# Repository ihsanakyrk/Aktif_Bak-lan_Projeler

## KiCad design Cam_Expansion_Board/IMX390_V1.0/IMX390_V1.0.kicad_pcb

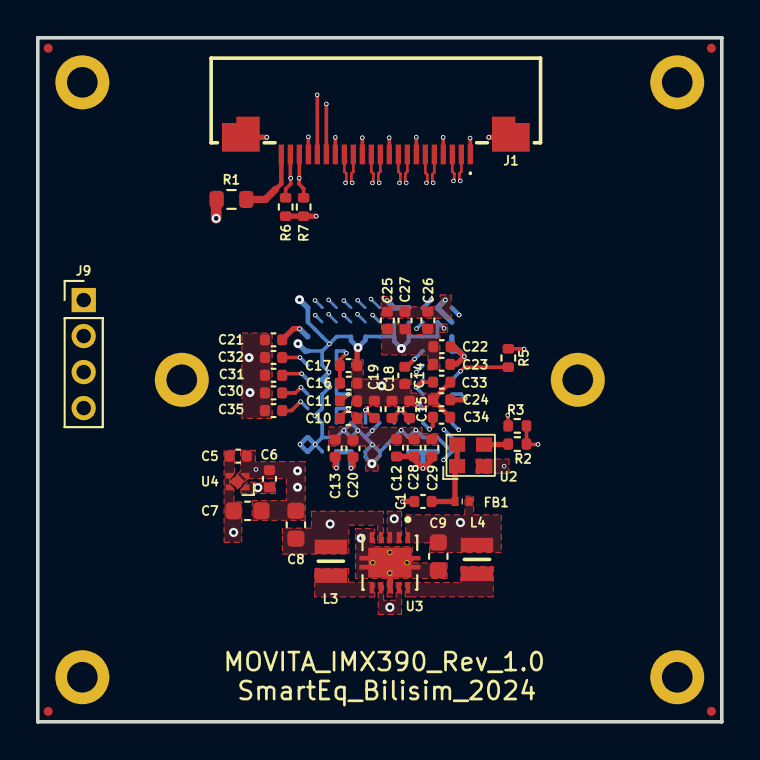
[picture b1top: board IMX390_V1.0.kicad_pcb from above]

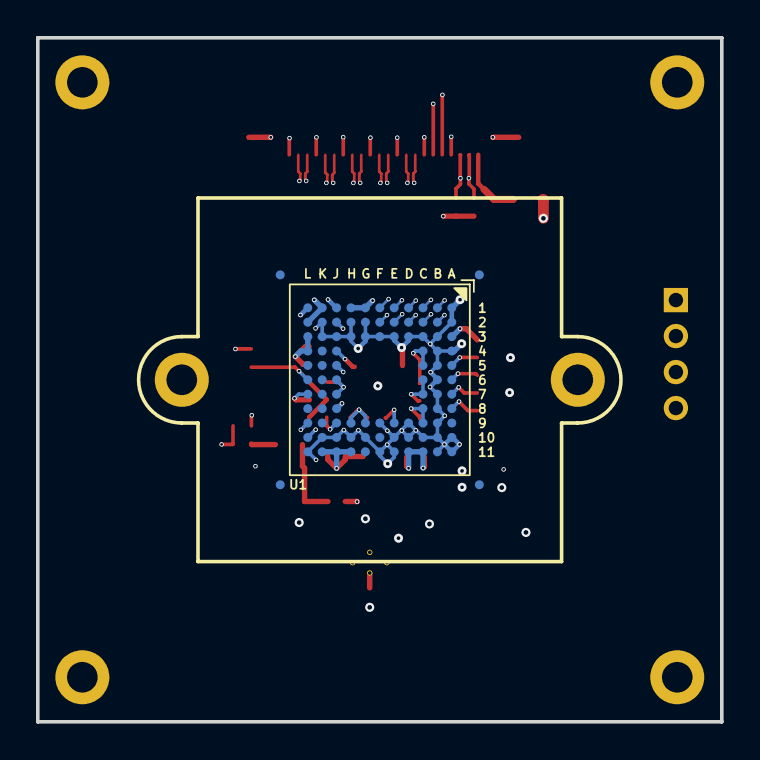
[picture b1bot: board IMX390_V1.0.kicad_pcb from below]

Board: 6 copper layers, 38.0 x 38.0 mm, 61 parts (5 on the bottom side), 33 nets.

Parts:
C1: 0.1uF 16V; C_0402_1005Metric
C5, C6, C10, C12, C18, C25, C28, C30, C31, C32, C34: 1.0µF 6.3V; C_0402_1005Metric
C7, C8, C9: 10uF 10V; C_0603_1608Metric
C11, C13, C15, C17, C19, C21, C23, C26, C29, C35: 0.1µF 16V; C_0402_1005Metric
C14, C16, C20, C22: 4.7µF 16V; C_0402_1005Metric
C24, C27: 0.01uF 6.3V; C_0402_1005Metric
C33: 0.22uF 10V; C_0402_1005Metric
FB1: BLM15AG221SN1D; NFZ15SG152SN10B
FID1, FID2, FID3, FID4, FID5, FID6, FID7, FID8: Fiducial; Fiducial_0.5mm_Mask1mm
J1: FFC SOCKET DR_BOTTOM 0.5MM -22P; F32R1A7H111022
J3, J4, J5, J6, J7, J8: DNP; Screw
J9: DNP; PinHeader_1x04_P2.00mm_Vertical
L3, L4: 2.2µH; LQM2MPN1R0NG0L
R1: 0R; R_0603_1608Metric
R2: 22R; R_0402_1005Metric
R3, R6, R7: DNP; R_0402_1005Metric
R5: 0R; R_0402_1005Metric
U1: IMX390CQV-W; IMX390CQV_W
U2: 1NM27000C33YC
U3: TPS62423QDRCRQ1; SON50P300X300X100-11N
U4: LP5907SNX-2.9/NOPB; X2-SON-4-EP

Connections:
1V2: C8.1, C12.1, C13.1, C20.1, C21.1, C25.1, C26.1, C27.2, C28.1, C29.1, L3.2, U1.A3 (VDDLSC), U1.C11 (VDDLCN), U1.D11 (VDDLSC), U1.G1 (VDDLIF), U1.H1 (VDDLIF), U1.H11 (VDDLCN), U1.J11 (VDDLPLAD), U1.K1 (VDDLSC), U1.K11 (VDDLPAD), U1.L2 (VDDLSC), U3.4 (FB1)
1V8: C9.1, C22.2, C23.2, C24.2, FB1.1, L4.2, R6.2, R7.2, U1.L3 (VDDMIO), U1.L4 (VDDMIO), U1.L7 (XCE), U3.1 (ADJ2)
2V9: C6.1, C10.1, C11.1, C14.1, C15.1, C16.1, C17.1, C18.1, C19.1, U1.C4 (VDDHPX), U1.C5 (VDDHCP), U1.C6 (VDDHCP), U1.C7 (VDDHAN), U1.C8 (VDDHAN), U1.C9 (VDDHPX), U1.E9 (VDDHCM), U1.G9 (VDDHCM), U1.H9 (VDDHPX), U1.J4 (VDDHPX), U4.1 (VOUT)
3V3: C5.1, C7.1, R1.1, U3.2 (MODE/DATA), U3.3 (VIN), U3.7 (EN1), U3.9 (EN2), U4.3 (EN), U4.4 (VIN)
/IMX390/CSI0_CLK_N: J1.8, U1.D2 (DMCKM)
/IMX390/CSI0_CLK_P: J1.9, U1.D1 (DMCKP)
/IMX390/CSI0_D0_N: J1.2, U1.E2 (DMOMA)
/IMX390/CSI0_D0_P: J1.3, U1.E1 (DMOPA)
/IMX390/CSI0_D1_N: J1.5, U1.C2 (DMOMB)
/IMX390/CSI0_D1_P: J1.6, U1.C1 (DMOPB)
/IMX390/CSI0_D2_N: J1.11, U1.F2 (DMOMC)
/IMX390/CSI0_D2_P: J1.12, U1.F1 (DMOPC)
/IMX390/CSI0_D3_N: J1.14, U1.B2 (DMOMD)
/IMX390/CSI0_D3_P: J1.15, U1.B1 (DMOPD)
/IMX390/EXT_XVCLK: J1.17, R3.2
/IMX390/FSIN: R5.1, U1.L6 (FSYNC)
/IMX390/SCL: J1.20, R7.1, U1.L10 (SCK)
/IMX390/SDA: J1.21, R6.1, U1.L9 (SDI)
/IMX390/SYS_CLEAR: J9.1, U1.J2 (XCLR)
/IMX390/XCLK: R2.2, R3.1, U1.J1 (INCK)
GND: C1.2, C5.2, C6.2, C7.2, C8.2, C9.2, C10.2, C11.2, C12.2, C13.2, C14.2, C15.2, C16.2, C17.2, C18.2, C19.2, C20.2, C21.2, C22.1, C23.1, C24.1, C25.2, C26.2, C27.1, C28.2, C29.2, C30.2, C31.2, C32.2, C33.2, C34.2, C35.2, J1.1, J1.4, J1.7, J1.10, J1.13, J1.16, J1.19, J1.23, J1.24, J3.1, J4.1, J5.1, J6.1, J7.1, J8.1, U1.A1 (VSSLSC), U1.A2 (VSSLSC), U1.A4 (VSSHCP), U1.A10 (VSSHCM), U1.A11 (VSSLSC), U1.B3 (VSSLIF), U1.B4 (VSSHPX), U1.B5 (VSSHCP), U1.B6 (VSSHCP), U1.B7 (VSSHAN), U1.B8 (VSSHAN), U1.B9 (VSSHPX), U1.B10 (VSSHCM), U1.B11 (VSSLSC), U1.C3 (VSSLIF), U1.C10 (VSSLCN), U1.D3 (VSSLIF), U1.D9 (VSSHCM), U1.D10 (VSSLSC), U1.E3 (VSSLIF), U1.E10 (SLASEL1), U1.E11 (SLASEL2), U1.F3 (VSSLIF), U1.F9 (VSSHCM), U1.F11 (SLASEL0), U1.G2 (VSSLIF), U1.G3 (VSSLIF), U1.G10 (CMODE), U1.H2 (VSSLSC), U1.H3 (VSSLSC), U1.H10 (VSSLCN), U1.J3 (VSSLSC), U1.J5 (VSSHPX), U1.J8 (VSSHPX), U1.J10 (VSSLPLAD), U1.K2 (VSSLSC), U1.K3 (VSSLSC), U1.K10 (VSSLPLAD), U1.L1 (VSSLSC), U1.L11 (VSSLSC), U2.2 (GND), U3.5 (DEF_1), U3.8 (GND), U3.11 (PAD), U4.2 (GND), U4.5 (EP)
unnamed: J1.18, R5.2
unnamed: J1.22, R1.2
unnamed: C32.1, U1.A5 (VCAPI1)
unnamed: C31.1, U1.A6 (VCAPI2)
unnamed: C30.1, U1.A7 (VCAPI3)
unnamed: C33.1, U1.J6 (VCAPI4), U1.J7 (VCAPI5)
unnamed: C34.1, U1.J9 (VCAPIO1)
unnamed: C35.1, U1.A8 (VCAPIO2)
unnamed: C1.1, FB1.2, U2.1 (OE), U2.4 (VDD)
unnamed: R2.1, U2.3 (OUT)
unnamed: L3.1, U3.6 (SW1)
unnamed: L4.1, U3.10 (SW2)

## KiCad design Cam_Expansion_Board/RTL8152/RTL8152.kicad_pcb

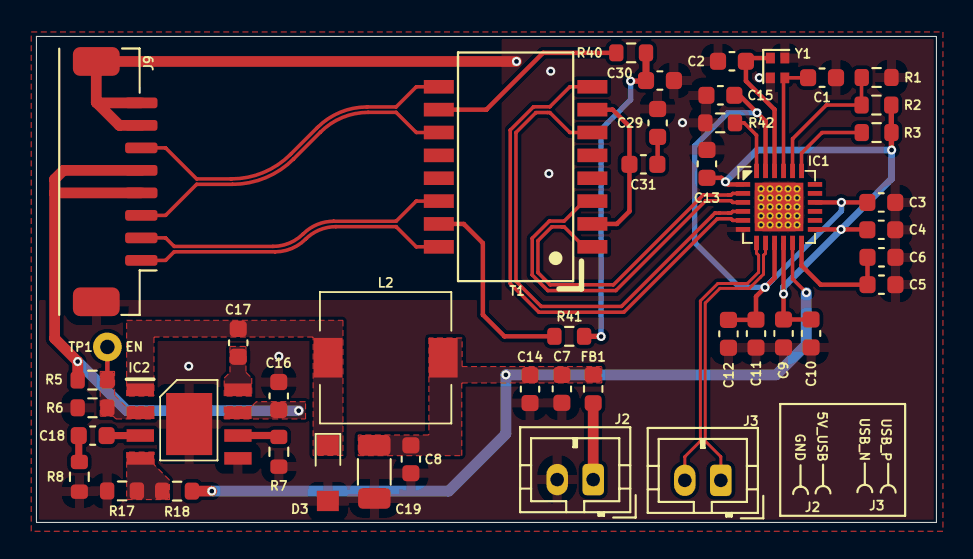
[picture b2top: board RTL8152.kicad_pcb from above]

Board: 2 copper layers, 50.0 x 27.0 mm, 45 parts (0 on the bottom side), 34 nets.

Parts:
C1, C2: 22pF; C_0603_1608Metric
C3, C4, C5, C7, C9, C11, C13, C15, C17: 100nF; C_0603_1608Metric
C6: 1uF; C_0603_1608Metric
C8, C10, C12: 4.7uF; C_0603_1608Metric
C14, C29, C31: 10nF; C_0603_1608Metric
C16: 10uF; C_0603_1608Metric
C18: 150pF; C_0603_1608Metric
C19: 22uF/6.3V; C_1206_3216Metric
C30: 1nF; C_0603_1608Metric
D3: SS34C-MD; SS34FA
FB1: BLM18AG102SN1D; 0603_Ferrite Beads
IC1: RTL8152B-VB-CG; QFN50P400X400X90-25N
IC2: MP1584EN-LF-Z; MP1584N
J2, J3: B2B-PH-K-S(LF)(SN); JST_PH_B2B-PH-K_1x02_P2.00mm_Vertical
J9: DS1020-03-08MVT1-R; JST_GH_BM08B-GHS-TBT_1x08-1MP_P1.25mm_Vertical
L2: SRI0704-100M
R1, R2, R3: 10K; R_0603_1608Metric
R5, R7, R8: 100K; R_0603_1608Metric
R6: 24.9K; R_0603_1608Metric
R17: 40.2K; R_0603_1608Metric
R18: 210K; R_0603_1608Metric
R40, R41, R42: 75R; R_0603_1608Metric
T1: H1102NL
TP1: DNP; Test_Point
Y1: RH100-25.000-20-F-1010-T; Oscillator_SMD_Abracon_ASCO-4Pin_1.6x1.2mm

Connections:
5V_LAN: C7.2 (-), C8.2 (-), C14.2 (-), C19.1, FB1.1, IC1.11 (VDD5), L2.2, R18.2
5V_USB: FB1.2, J2.1
/N1: IC1.3 (MDIN0), T1.3 (TD-)
/N2: IC1.5 (MDIN1), T1.8 (RD-)
/P1: IC1.2 (MDIP0), T1.1 (TD+)
/P2: IC1.4 (MDIP1), T1.6 (RD+)
/U2DN: IC1.7 (U2DM), J3.2
/U2DP: IC1.8 (U2DP), J3.1
/XIN_1: C2.1 (+), IC1.22 (CKXTAL2), Y1.1 (CRYSTAL_1)
/XOUT_1: C1.2 (-), IC1.21 (CKXTAL1), Y1.3 (CRSYTAL_2)
GND: C1.1 (+), C2.2 (-), C3.1 (+), C4.1 (+), C5.1 (+), C6.1 (+), C7.1 (+), C8.1 (+), C9.1 (+), C10.1 (+), C11.1 (+), C12.1 (+), C13.1 (+), C14.1 (+), C15.1 (+), C16.1, C19.2, C29.2, C30.2, D3.2, IC1.6 (U2GND), IC1.25 (EP), IC2.5 (GND), IC2.9 (EP), J2.2, J9.7, J9.8, J9.MP, R1.2, R6.2, R7.2, R8.2, R17.2, R42.2, Y1.2 (GND_1), Y1.4 (GND_2)
unnamed: C18.1, R8.1
unnamed: C29.1, C31.2
unnamed: C30.1, R40.1, R41.2
unnamed: IC1.19 (LANWAKEB), R3.1
unnamed: IC1.24 (RSET), R42.1
unnamed: IC1.20 (SPISDO), R1.1, R2.1
unnamed: C17.2, IC2.8 (BST)
unnamed: C18.2, IC2.3 (COMP)
unnamed: IC2.2 (EN), R5.2, R6.1, TP1.1
unnamed: IC2.4 (FB), R17.1, R18.1
unnamed: IC2.6 (FREQ), R7.1
unnamed: C17.1, D3.1, IC2.1 (SW), L2.1
unnamed: C31.1, T1.2 (CT1), T1.7 (CT2)
unnamed: R40.2, T1.10 (CT3)
unnamed: R41.1, T1.15 (CT4)
TRD0_N: J9.2, T1.14 (TX-)
TRD0_P: J9.1, T1.16 (TX+)
TRD1_N: J9.6, T1.9 (RX-)
TRD1_P: J9.3, T1.11 (RX+)
VDD3V3: C4.2 (-), C9.2 (-), C10.2 (-), C13.2 (-), IC1.1 (AVDD33_1), IC1.10 (AVDD33_2), IC1.13 (DVDD33), R2.2, R3.2
VDD10: C3.2 (-), C11.2 (-), C12.2 (-), C15.2 (-), IC1.9 (U2VDD10), IC1.16 (DVDD10), IC1.23 (AVDD10)
VDD10_UPS: C5.2 (-), C6.2 (-), IC1.12 (DVDD10_UPS)
VRAW: C16.2, IC2.7 (VIN), J9.4, J9.5, R5.1

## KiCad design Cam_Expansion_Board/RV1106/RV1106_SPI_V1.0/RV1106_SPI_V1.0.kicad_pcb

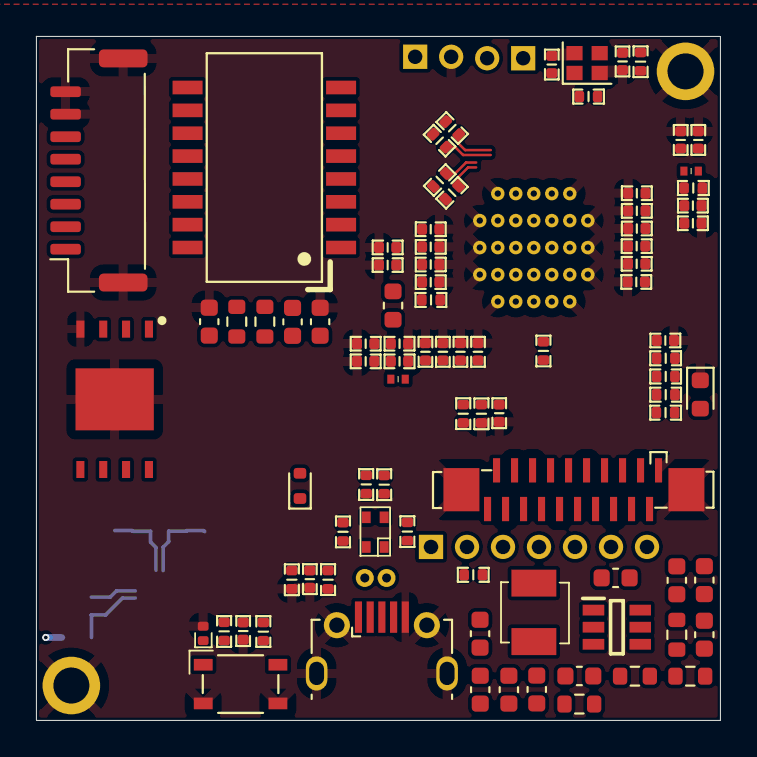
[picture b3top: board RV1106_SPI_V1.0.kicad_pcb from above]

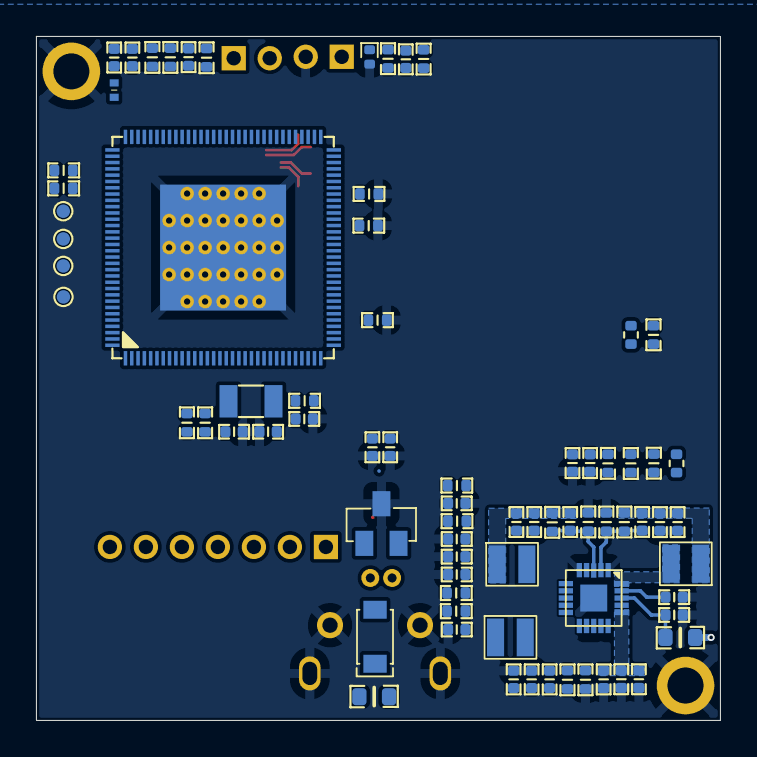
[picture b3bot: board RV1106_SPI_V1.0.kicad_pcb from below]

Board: 4 copper layers, 38.0 x 38.0 mm, 170 parts (76 on the bottom side), 110 nets.

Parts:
C1, C2, C6, C7: 18pF 50V C0G; C_0402_1005Metric
C3, C4, C5, C9, C10, C11, C16, C17, C18, C21, C25, C27, C29, C34, C36, C50, C51, C52, C54, C55, C72: 100nF X5R 16V; C_0402_1005Metric
C8, C14, C15, C20, C24, C26, C73: 1uF X5R 6.3V; C_0402_1005Metric
C12, C13, C19, C22, C23, C28, C62: 10uF X5R 6.3V; C_0402_1005Metric
C35: DNP; C_0402_1005Metric
C37, C42, C45: 220pF; C_0402_1005Metric
C38, C39, C43: 4.7uF; C_0402_1005Metric
C40, C41, C44, C46, C47, C48, C49: 10uF 10V; C_0402_1005Metric
C53, C71: 4.7uF X5R 6.3V; C_0402_1005Metric
C63: 100nF X5R 6.3V; C_0402_1005Metric
C74, C75: 0.01uF; C_0603_1608Metric
C76: 1000pF; C_0603_1608Metric
C77, C78, C79, C81: 1nF C0G 50V; C_0402_1005Metric
C80, C82: 10uF 25V X5R; C_0603_1608Metric
C84: 100nF; C_0603_1608Metric
C85: 22pF; C_0603_1608Metric
C86, C87: 22uF 16V X5R; C_0603_1608Metric
C88, C89, C90: 100nF 16V X5R; C_0603_1608Metric
D1: RB521S-30; D_SOD-523
D2: LED_White; LED_0603_1608Metric
D32: MBR230LSFT1G; SS14
D34, D35: ESD5451N; ESD5341N
ESD1: ESD5302F; SOT-23-Diode
FB1: DNP; SMD-4P,2.0x1.2mm
IC3: SY8113B
J1, J3: DNP; Min_Screw
J2: DNP; PinHeader_1x07_P2.00mm_Vertical
J4, J5: DNP; PinHeader_1x02_P2.00mm_Vertical
J13: JST_1x8-1MP_P1.25mm_Vertical; JST_1x8_1MP_P1.25mm_Vertical
J20: MICRO XNJ ZB; Micro-B SMD
J28: AFC11-S20ICA-00
L1, L2, L7: BLM15PD121SN1; Feritte_Beads_0402
L4, L5, L6: FTC252012S1R5MBCA
L8: CBG160808U000T; 0603_Ferrite Beads
L9: HA42-4R7MT
R1: 1M %5; R_0402_1005Metric
R2, R4, R6, R7, R21, R22: 22R %5; R_0402_1005Metric
R3, R28, R42: 100R %5; R_0402_1005Metric
R5, R26: 1R %5; R_0402_1005Metric
R10, R18, R25, R29, R30, R31, R32, R48, R49, R57, R58, R61, R63, R69: 0R; R_0402_1005Metric
R11: 100K %5; R_0603_1608Metric
R12, R27, R55, R56, R59: 10K %5; R_0402_1005Metric
R13: 200K; R_0402_1005Metric
R14: 40.2K %1; R_0402_1005Metric
R15: 9.1K %1; R_0402_1005Metric
R16: 47K %1; R_0402_1005Metric
R17, R20: 100K %1; R_0402_1005Metric
R19: 200K %1; R_0402_1005Metric
R23: 240R %1; R_0402_1005Metric
R24: 6.04K %1; R_0402_1005Metric
R33: 1K %5; R_0402_1005Metric
R43, R44: 4.7K %5; R_0402_1005Metric
R45: DNP; R_0603_1608Metric
R46, R47: 2.2R %5; R_0402_1005Metric
R50, R60, R62, R66, R67, R68: DNP; R_0402_1005Metric
R64: 10K; R_0402_1005Metric
R65: 15K; R_0402_1005Metric
R70, R71: 75R; R_0603_1608Metric
R75: 110K; R_0603_1608Metric
R76: 15K; R_0603_1608Metric
R77: 120K; R_0603_1608Metric
R78: 30K; R_0603_1608Metric
S5: SKRPANE010
T1: H1102NL
TP1, TP2: DNP; Test_Point
TP6, TP7, TP8, TP9: DNP; TestPoint_Pad_D0.75
U1: RV1106G3
U3: EA3036C
U5: W25N02KVZEIR; SON127P800X600X80-9N-D
U7: 24MHz; Crystal_SMD_2016-4Pin_2.0x1.6mm
Y1: Crystal_32.768kHz; Crystal_SMD_3215-2Pin_3.2x1.5mm

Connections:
/DN: ESD1.2, FB1.4, J20.2 (DM), R48.2, TP1.1
/DP: ESD1.1, FB1.1, J20.3 (DP), R49.2, TP2.1
/EN1: C36.1, R13.2, U3.9 (EN1)
/EN2: C35.1, R12.2, U3.8 (EN2)
/EN3: C34.1, R11.2, U3.18 (EN3)
/ETH_R_N: R32.1, U1.97 (FEPHY_RXN)
/ETH_R_P: R31.1, U1.98 (FEPHY_RXP)
/ETH_T_N: R30.1, U1.99 (FEPHY_TXN)
/ETH_T_P: R29.1, U1.100 (FEPHY_TXP)
/FSPI_CLK: R21.1, U5.6 (CLK)
/FSPI_CS0N: U1.47 (FSPI_CS0_EMMC_CMD_GPIO4_B0_u), U5.1 (~CS)
/FSPI_D0: R67.2, U1.41 (FSPI_D0_EMMC_D0_GPIO4_A4_u), U5.5 (DI(D0))
/FSPI_D1: R68.2, U1.42 (FSPI_D1_EMMC_D1_GPIO4_A3_u), U5.2 (DO(D1))
/FSPI_D2: R55.2, U1.44 (FSPI_D2_EMMC_D2_GPIO4_A2_u), U5.3 (~WP(D2))
/FSPI_D3: R56.2, U1.39 (FSPI_D3_EMMC_D3_GPIO4_A6_u), U5.7 (~HOLD(D3))
/GPIO3_C6_d: R7.2, R50.1, U1.4 (VI_BT656_D2_M0_VI_BT1120_D10_PWM7_IR_M2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)
/GPIO4_C1_z: C79.1, R59.2, R60.1, U1.22 (PWM1_M1_SARADC_IN1_GPIO4_C1_z)
/MIPI_CSI_AVDD_1V8: C11.1, R5.2, U1.1 (MIPI_AVDD1V8_VCCIO7_VCC1V8)
/MIPI_I2C_SCL: J28.13, R43.1, U1.5 (VI_BT656_D3_M0_VI_BT1120_D11_UART5_TX_M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)
/MIPI_I2C_SDA: J28.14, R44.1, U1.7 (VI_BT656_D4_M0_VI_BT1120_D12_UART5_RX_M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)
/MIPI/LVDS_CLK_N: J28.8, U1.125 (VI_BT656_D0_M0_VI_BT1120_D8_LVDS_RX_CLK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)
/MIPI/LVDS_CLK_P: J28.7, U1.126 (VI_BT656_D1_M0_VI_BT1120_D9_LVDS_RX_CLK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)
/MIPI/LVDS_D0_N: J28.5, U1.127 (VI_BT656_CLK_M0_VI_BT1120_CLK_LVDS_RX_D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)
/MIPI/LVDS_D0_P: J28.4, U1.128 (LVDS_RX_D0P_MIPI_CSI_RX_D0P_VI_CIF_HREF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)
/MIPI/LVDS_D1_N: J28.11, U1.123 (VI_BT1120_D6_LVDS_RX_D1N_MIPI_CSI_RX_D1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)
/MIPI/LVDS_D1_P: J28.10, U1.124 (VI_BT1120_D7_LVDS_RX_D1P_MIPI_CSI_RX_D1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)
/MIPI/LVDS_MCLK0: J28.2, R6.1
/MIPI/LVDS_RST: J28.16, U1.3 (VI_CIF_VSYNC_M0_GPIO3_C5_d)
/NPOR: C78.1, R33.2, R42.1, U1.66 (nPOR)
/RECOVERY: C77.1, R27.2, R28.1, U1.23 (SARADC_IN0_GPIO4_C0_z)
/RX_P0+: R31.2, T1.6 (RD+)
/RX_P0-: R32.2, T1.8 (RD-)
/SDMMC_CLK: J2.4, R22.1
/SDMMC_CMD: J2.3, U1.16 (JTAG_LPMCU_TMS_M1_I2C0_SDA_M2_PWM11_IR_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)
/SDMMC_D0: J2.5, U1.14 (PWM8_M0_UART2_RX_M0_SDMMC_D0_GPIO3_A3_u)
/SDMMC_D1: J2.6, U1.12 (PWM9_M0_UART2_TX_M0_SDMMC_D1_GPIO3_A2_u)
/SDMMC_D2: J2.1, U1.18 (JTAG_HPMCU_TCK_M1_JTAG_CPU_TCK_M0_UART5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)
/SDMMC_D3: J2.2, U1.17 (JTAG_HPMCU_TMS_M1_JTAG_CPU_TMS_M0_UART5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)
/SDMMC_DET: J2.7, U1.11 (SDMMC_DET_GPIO3_A1_u)
/TX_P0+: R29.2, T1.1 (TD+)
/TX_P0-: R30.2, T1.3 (TD-)
/UART1_CTS: TP7.1, U1.109 (I2C4_SDA_M0_UART1_CTS_M1_VO_LCDC_D8_I2S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)
/UART1_RTS: TP6.1, U1.110 (I2C4_SCL_M0_UART1_RTS_M1_VO_LCDC_D9_I2S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)
/UART1_RX: TP8.1, U1.114 (UART1_RX_M1_VO_LCDC_D13_I2S0_SDI0_SDIO_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)
/UART1_TX: TP9.1, U1.113 (UART1_TX_M1_VO_LCDC_D12_I2S0_SDO0_SDIO_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)
/UART2_RX: J4.1, U1.80 (JTAG_HPMCU_TMS_M0_JTAG_LPMCU_TMS_M0_JTA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)
/UART2_TX: J4.2, U1.79 (JTAG_HPMCU_TCK_M0_JTAG_LPMCU_TCK_M0_JTA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)
/USB_DET_IN: C81.1, R64.2, R65.1, U1.25 (USB_VBUSDET)
/USB_N: R46.1, U1.26 (USB_DM)
/USB_P: R47.1, U1.27 (USB_DP)
/USB_VIN: D32.A, J20.1 (VBUS), R64.1
Earth: C80.1, C82.1, C86.1, C87.1, C88.1, C89.1, C90.1, IC3.2 (GND), R76.2, R78.2
GND: C1.2, C2.1, C3.2, C4.2, C5.2, C6.2, C7.2, C8.2, C9.2, C10.2, C11.2, C12.2, C13.2, C14.2, C15.2, C16.2, C17.2, C18.2, C19.2, C20.2, C21.2, C22.2, C23.2, C24.2, C25.2, C26.2, C27.2, C28.2, C29.2, C34.2, C35.2, C36.2, C38.1, C39.1, C40.1, C41.1, C43.1, C44.1, C46.2, C47.2, C48.2, C49.2, C50.2, C51.2, C52.2, C53.2, C54.2, C55.2, C62.2, C63.2, C71.2, C72.2, C73.2, C75.2, C76.2, C77.2, C78.2, C79.2, C81.2, D2.1, D34.2, D35.2, ESD1.3, J1.1, J3.1, J5.2, J13.7, J13.8, J13.9, J13.10, J20.5 (GND), J20.6 (Shield), J28.1, J28.3, J28.6, J28.9, J28.12, J28.15, J28.17, J28.18, J28.21, J28.22, R15.2, R17.2, R20.2, R23.2, R24.2, R25.1, R58.1, R60.2, R65.2, S5.3, S5.4, U1.129 (ePAD), U3.1 (GND3), U3.4 (GND2), U3.5 (GND2), U3.12 (GND1), U3.13 (GND1), U3.15 (AGND), U3.17 (AGND), U3.21 (AGND), U5.4 (VSS), U5.9 (EPAD), U7.2 (GND), U7.4 (GND)
unnamed: C74.2, C75.1
unnamed: C76.1, R70.1, R71.1
unnamed: D1.1 (K), R3.1
unnamed: D2.2, R50.2
unnamed: D32.C, R45.2
unnamed: D34.1, R28.2, S5.1, S5.2
unnamed: FB1.2, R47.2, R49.1
unnamed: FB1.3, R46.2, R48.1
unnamed: C84.1, IC3.1 (BS)
unnamed: IC3.4 (EN), R77.2, R78.1
unnamed: C85.1, IC3.3 (FB), R75.2, R76.1
unnamed: C84.2, IC3.6 (LX), L9.1
unnamed: D35.1, J5.1, R42.2
unnamed: J28.19, J28.20, R10.1
unnamed: C74.1, T1.2 (CT1), T1.7 (CT2)
unnamed: R70.2, T1.10 (CT3)
unnamed: R71.2, T1.15 (CT4)
unnamed: C6.1, U1.21 (OSC_RTC_XIN), Y1.1
unnamed: C7.1, U1.20 (OSC_RTC_XOUT), Y1.2
unnamed: C2.2, R1.1, U1.68 (OSC_SOC_XIN), U7.1 (X1)
unnamed: R1.2, R2.2, U1.69 (OSC_SOC_XOUT)
unnamed: L1.1, U1.96 (OTP_AVDD1V8_ETH_AVDD1V8_TSADC_AVDD1V8)
unnamed: C8.1, R3.2, U1.19 (RTC_AVDD3V3)
unnamed: R58.2, U1.57 (TVSS)
unnamed: R21.2, U1.48 (FSPI_CLK_EMMC_CLK_GPIO4_B1_d)
unnamed: R22.2, U1.15 (JTAG_LPMCU_TCK_M1_I2C0_SCL_M2_PWM10_M0_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)
unnamed: C50.1, R57.2, U1.43 (VCCIO3_VCC)
unnamed: R4.2, U1.85 (I2C3_SCL_M1_AUD_DSM_N_UART5_TX_M1_PWM11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)
unnamed: R6.2, U1.2 (MIPI_CLK0_OUT_VI_CIF_CLKO_M0_GPIO3_C4_d)
unnamed: R61.2, R62.2, U1.108 (VCCIO5_VCC)
unnamed: R63.2, R66.2, U1.88 (VCCIO6_VCC)
unnamed: R25.2, U1.37 (CODEC_AVSS)
unnamed: C53.1, U1.30 (CODEC_VCM)
unnamed: R23.1, U1.52 (DRAM_ZQ)
unnamed: L7.2, U1.101 (FEPHY_AVDD3V3)
unnamed: R24.1, U1.102 (FEPHY_REXT)
unnamed: C54.1, R26.2, U1.24 (SARADC_USB_AVDD1V8)
unnamed: C37.2, R14.1, R15.1, U3.14 (FB1)
unnamed: C42.2, R16.1, R17.1, U3.3 (FB2)
unnamed: C45.2, R19.1, R20.1, U3.2 (FB3)
unnamed: L5.2, U3.6 (LX2)
unnamed: L6.2, U3.20 (LX3)
unnamed: L4.2, U3.11 (LX)
unnamed: R69.1, U5.8 (VCC)
unnamed: C1.1, R2.1, U7.3 (X2)
RX0_N: J13.6, T1.9 (RX-)
RX0_P: J13.3, T1.11 (RX+)
TRD0_N: J13.2, T1.14 (TX-)
TRD0_P: J13.1, T1.16 (TX+)
VCC1V8_CODEC: C28.1, C29.1, L2.2, U1.31 (CODEC_AVDD1V8)
VCC5V0_SYS: C46.1, C47.1, C48.1, C49.1, C85.2, C86.2, C87.2, C88.2, C89.2, L9.2, R11.1, R12.1, R13.1, R45.1, R75.1, U3.7 (VIN2), U3.10 (VIN1), U3.16 (VCC), U3.19 (VIN3)
VCC_1V8: C3.1, C4.1, C26.1, C27.1, C71.1, C72.1, L1.2, L2.1, L8.1, R5.1, R26.1, R27.1, R43.2, R44.2, R59.1, R62.1, R66.1, U1.53 (DDR_PLL_AVDD1V8), U1.70 (OSC_AVDD1V8_PLL_AVDD1V8)
VCC_3V3: C9.1, C10.1, C37.1, C38.2, C39.2, C51.1, C52.1, C55.1, C62.1, C63.1, D1.2 (A), L4.1, L7.1, R10.2, R14.2, R33.1, R55.1, R56.1, R57.1, R61.1, R63.1, R67.1, R68.1, R69.2, U1.13 (VCCIO4_VCC), U1.28 (USB_AVDD3V3), U1.61 (PMU_VCC3V3), U1.81 (VCCIO1_VCC3V3)
VCC_DDR: C22.1, C23.1, C24.1, C25.1, C43.2, C44.2, C45.1, C73.1, L6.1, L8.2, R19.2, U1.49 (DDR_VDDQ_1), U1.50 (DDR_VDDQ_2), U1.56 (DDR_VDDQ_3)
VDD_0V9: C5.1, C12.1, C13.1, C14.1, C15.1, C16.1, C17.1, C18.1, C40.2, C41.2, C42.1, L5.1, R16.2, R18.1, U1.10 (DVDD_1), U1.51 (DVDD_2), U1.54 (DVDD_3), U1.55 (DVDD_4), U1.67 (OSC_DVDD0V9_PMU_DVDD0V9), U1.71 (PLL_DVDD0V9), U1.82 (DVDD_5), U1.103 (DVDD_6), U1.116 (DVDD_7)
VDD_ARM: C19.1, C20.1, C21.1, R18.2, U1.115 (CPU_DVDD)
VIN: C80.2, C82.2, C90.2, IC3.5 (IN), J13.4, J13.5, R77.1

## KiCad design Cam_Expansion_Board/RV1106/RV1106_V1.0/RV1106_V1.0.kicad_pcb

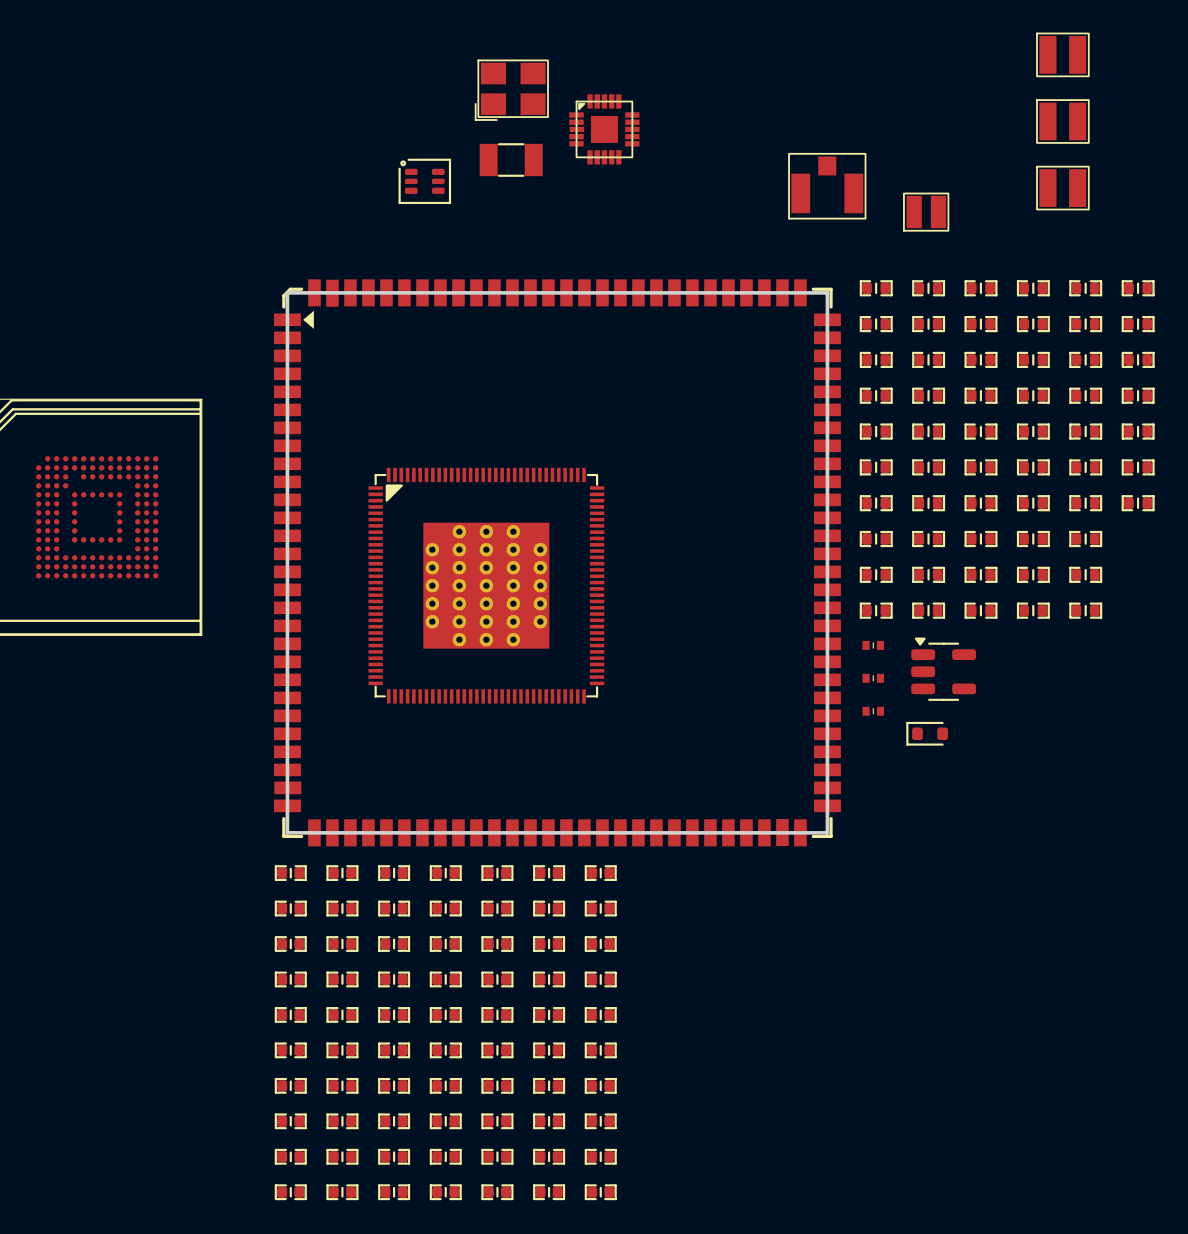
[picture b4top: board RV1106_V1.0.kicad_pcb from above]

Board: 2 copper layers, 144 parts (0 on the bottom side), 163 nets, no tracks yet.

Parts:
C1, C2: 18pF C0G; C_0402_1005Metric
C3, C4: 100nF X5R; C_0402_1005Metric
C5, C9, C10, C11, C16, C17, C18, C21, C25, C27, C29, C34, C36, C50, C51, C52, C54, C55, C63, C64, C65, C66, C68, C69: 100nF 16V X5R; C_0402_1005Metric
C6, C7: 18pF 50V C0G; C_0402_1005Metric
C8, C14, C15, C20, C24, C26, C62: 1uF 6.3V X5R; C_0402_1005Metric
C12, C13, C19, C22, C23, C28: 10uF 6.3V X5R; C_0402_1005Metric
C30, C46, C47, C48, C49: 10uF 10V; C_0402_1005Metric
C31, C33: 100nF; C_0402_1005Metric
C32, C40, C41, C44, C56, C59, C61: 10uF; C_0402_1005Metric
C35, C58: DNP; C_0402_1005Metric
C37, C42, C45: 220pF; C_0402_1005Metric
C38, C39, C43: 4.7uF; C_0402_1005Metric
C53, C67, C70: 4.7uF 6.3V X5R; C_0402_1005Metric
C57: 10pF; C_0402_1005Metric
C60: 10uF/10V; C_0402_1005Metric
D1: RB521S-30; D_SOD-523
J1: IPEX1-3-TXZ 214
L1, L2, L7: BLM15PD121SN1; Feritte_Beads_0402
L3: PIM201610-1R0MTS00; SMD,2x1.6x1mm_Power_Inductor
L4, L5, L6: FTC252012S1R5MBCA
R1: 1M %5; R_0402_1005Metric
R2, R4, R6, R7, R21, R22: 22R %5; R_0402_1005Metric
R3: 100R %5; R_0402_1005Metric
R5, R26: 1K %5; R_0402_1005Metric
R8: 100K; R_0402_1005Metric
R9: 100K %1; R_0402_1005Metric
R10: 127K %1; R_0402_1005Metric
R11: 100K %5; R_0402_1005Metric
R12, R55, R56: 10K %5; R_0402_1005Metric
R13: 200K; R_0402_1005Metric
R14: 40.2K %1; R_0402_1005Metric
R15: 9.1K %1; R_0402_1005Metric
R16: 47K %1; R_0402_1005Metric
R17, R20: 100K 1%; R_0402_1005Metric
R18, R25: 0R %5; R_0402_1005Metric
R19: 200K %1; R_0402_1005Metric
R23: 240R %1; R_0402_1005Metric
R24: 6.04K %1; R_0402_1005Metric
R27, R28: 4.7K; R_0402_1005Metric
R29: 10K; R_0402_1005Metric
R30, R31, R32, R33: 1K; R_0402_1005Metric
R34, R35, R36, R37, R38, R39, R40, R41, R42, R43, R44, R45, R46, R47, R48, R49, R50, R51, R52, R53, R54: 0R; R_0402_1005Metric
R57: 4.7K %5; R_0402_1005Metric
U1: RV1106G3
U2: MP1605GTF-Z; SOT-563
U3: EA3036C
U5: DNP; Core1106-SMT
U7: 24MHz; SMD3225-4P
U8: ME6217C33M5G; SOT-23-5
U9: EMMC_B153_2L; EMMC
Y1: Crystal_32.768kHz; Crystal_SMD_3215-2Pin_3.2x1.5mm

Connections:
3V3: C56.1, C59.1, C61.1, R27.2, R28.2, U8.5 (OUT)
/EMMC_CLK: R21.1, R43.2, U9.M6 (CLK)
/EMMC_CMD: R42.2, U1.47 (FSPI_CS0_EMMC_CMD_GPIO4_B0_u)
/EMMC_D0: R34.2, R55.1, U1.41 (FSPI_D0_EMMC_D0_GPIO4_A4_u), U9.A3 (DATA0)
/EMMC_D1: R35.2, U1.42 (FSPI_D1_EMMC_D1_GPIO4_A3_u), U9.A4 (DATA1)
/EMMC_D2: R36.2, U1.44 (FSPI_D2_EMMC_D2_GPIO4_A2_u), U9.A5 (DATA2)
/EMMC_D3: R37.2, U1.39 (FSPI_D3_EMMC_D3_GPIO4_A6_u), U9.B2 (DATA3)
/EMMC_D4: R38.2, U1.40 (SPI1_CS0_M0_I2C2_SDA_M1_UART1_TX_M2_EMM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), U9.B3 (DATA4)
/EMMC_D5: R39.2, U1.38 (SPI1_CLK_M0_I2C2_SCL_M1_UART1_RX_M2_EMM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), U9.B4 (DATA5)
/EMMC_D6: R40.2, U1.45 (SPI1_MOSI_M0_I2C0_SCL_M1_UART0_TX_M2_EM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), U9.B5 (DATA6)
/EMMC_D7: R41.2, R56.1, U1.46 (SPI1_MISO_M0_I2C0_SDA_M1_UART0_RX_M2_EM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), U9.B6 (DATA7), U9.M5 (CMD)
/EN1: C36.1, R13.2, U3.9 (EN1)
/EN2: C35.1, R12.2, U3.8 (EN2)
/EN3: C34.1, R11.2, U3.18 (EN3)
/ETH_R_N: U1.97 (FEPHY_RXN), U5.85
/ETH_R_P: U1.98 (FEPHY_RXP), U5.86
/ETH_T_N: U1.99 (FEPHY_TXN), U5.87
/ETH_T_P: U1.100 (FEPHY_TXP), U5.88
/FLASH_ALE/EMMC_RST: R57.1, U9.K5 (RST_n)
/GPIO0_A0_z: U1.58 (RTC_CLK_OUT_CLK_32K_IN_REF_CLK_OUT_UART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), U5.58
/GPIO0_A1_d: U1.59 (PWM2_M0_UART0_TX_M0_GPIO0_A1_d), U5.59
/GPIO0_A2_d: R32.1, U1.60 (PWM3_IR_M0_GPIO0_A2_d), U5.60
/GPIO0_A3_u: R31.1, U1.62 (PWR_CTRL_M1_GPIO0_A3_u), U5.61
/GPIO0_A4_d: R30.1, U1.63 (PWM1_M0_PWR_CTRL_M0_GPIO0_A4_d), U5.62
/GPIO0_A5_d: R51.2, U1.64 (I2C1_SCL_M0_PWM5_M0_UART1_RTS_M0_GPIO0_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)
/GPIO0_A6_d: R52.2, U1.65 (I2C1_SDA_M0_PWM6_M0_UART1_CTS_M0_GPIO0_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)
/GPIO1_A0_d: U1.72 (I2C2_SCL_M0_PWM7_IR_M0_UART3_TX_M0_GPIO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), U5.65
/GPIO1_A1_d: U1.73 (I2C2_SDA_M0_PWM4_M0_UART3_RX_M0_GPIO1_A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), U5.66
/GPIO1_A2_d: R33.1, U1.74 (VI_CIF_D0_M1_CPU_AVS_PWM0_M0_GPIO1_A2_d), U5.67
/GPIO1_A3_d: R54.2, U1.75 (I2C0_SCL_M0_UART1_TX_M0_GPIO1_A3_d)
/GPIO1_A4_d: R53.2, U1.76 (I2C0_SDA_M0_UART1_RX_M0_GPIO1_A4_d)
/GPIO1_B0_d: U1.77 (PWM3_IR_M1_UART4_RX_M0_GPIO1_B0_d), U5.70
/GPIO1_B1_d: U1.78 (SPI1_CS1_M0_VI_CIF_D1_M1_PWM7_IR_M1_UAR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), U5.71
/GPIO1_B2_d: U1.79 (JTAG_HPMCU_TCK_M0_JTAG_LPMCU_TCK_M0_JTA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), U5.72
/GPIO1_B3_u: U1.80 (JTAG_HPMCU_TMS_M0_JTAG_LPMCU_TMS_M0_JTA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), U5.73
/GPIO1_C0_d: U1.95 (VI_BT656_D0_M1_SDIO_D1_M1_SPI0_CS0_M0_P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), U5.101
/GPIO1_C1_d: U1.94 (VI_BT656_D1_M1_SDIO_D0_M1_SPI0_CLK_M0_P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), U5.100
/GPIO1_C2_d: U1.93 (VI_BT656_D2_M1_I2C4_SCL_M1_SDIO_CLK_M1_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), U5.99
/GPIO1_C3_d: U1.92 (VI_BT656_D3_M1_I2C4_SDA_M1_SDIO_CMD_M1_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), U5.98
/GPIO1_C4_d: U1.91 (VI_BT656_D4_M1_SDIO_D3_M1_UART4_RX_M1_P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), U5.97
/GPIO1_C5_d: U1.90 (VI_BT656_D5_M1_SDIO_D2_M1_UART4_TX_M1_P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), U5.96
/GPIO1_C6_d: U1.83 (VI_BT656_D6_M1_UART4_RTS_M1_PWM10_M1_VI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), U5.95
/GPIO1_C7_d: U1.84 (VI_BT656_D7_M1_UART4_CTS_M1_PWM11_IR_M1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), U5.94
/GPIO1_D0_d: U1.89 (VI_BT656_CLK_M1_UART3_TX_M1_UART5_RTS_M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), U5.93
/GPIO1_D1_d: U1.87 (UART3_RX_M1_UART5_CTS_M1_PWM10_M2_VI_CI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), U5.92
/GPIO1_D2_d: U1.86 (SPI0_CS1_M0_I2C3_SDA_M1_AUD_DSM_P_UART5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), U5.91
/GPIO1_D3_d: R4.1, U5.90
/GPIO2_A0_d: U1.109 (I2C4_SDA_M0_UART1_CTS_M1_VO_LCDC_D8_I2S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), U5.102
/GPIO2_A1_d: U1.110 (I2C4_SCL_M0_UART1_RTS_M1_VO_LCDC_D9_I2S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), U5.103
/GPIO2_A2_d: U1.111 (VO_LCDC_D10_I2S0_MCLK_SDIO_CLK_M0_GPIO2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), U5.104
/GPIO2_A3_d: U1.112 (VO_LCDC_D11_I2S0_SDO3_SDI1_SDIO_CMD_M0_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), U5.105
/GPIO2_A4_d: U1.113 (UART1_TX_M1_VO_LCDC_D12_I2S0_SDO0_SDIO_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), U5.106
/GPIO2_A5_d: U1.114 (UART1_RX_M1_VO_LCDC_D13_I2S0_SDI0_SDIO_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), U5.107
/GPIO2_A6_d: U1.107 (FLASH_TRIGOUT_I2C3_SCL_M0_PWM2_M1_VO_LC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), U5.108
/GPIO2_A7_d: U1.106 (PRELIGHT_TRIGOUT_I2C3_SDA_M0_PWM4_M1_VO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), U5.109
/GPIO2_B0_d: U1.105 (PWM5_M1_VO_LCDC_D16_I2C1_SCL_M1_UART0_R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), U5.110
/GPIO2_B1_d: U1.104 (PWM6_M1_VO_LCDC_D17_I2C1_SDA_M1_UART0_T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), U5.111
/GPIO4_C0_z: U1.23 (SARADC_IN0_GPIO4_C0_z), U5.26
/GPIO4_C1_z: U1.22 (PWM1_M1_SARADC_IN1_GPIO4_C1_z), U5.27
/HOST_WAKE_BT: R27.1, R32.2
/LINEOUT: U1.29 (CODEC_LINEOUT), U5.30
/MIC0_N: U1.33 (CODEC_MIC0N), U5.32
/MIC0_P: U1.34 (CODEC_MIC0P), U5.33
/MIC1_N: U1.35 (CODEC_MIC1N), U5.34
/MIC1_P: U1.36 (CODEC_MIC1P), U5.35
/MIPI_CSI_AVDD_1V8: C11.1, R5.2, U1.1 (MIPI_AVDD1V8_VCCIO7_VCC1V8)
/MIPI_I2C3_SCL: U1.6 (VI_BT656_D5_M0_VI_BT1120_D13_UART5_RTS_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), U5.15
/MIPI_I2C3_SDA: U1.8 (VI_BT656_D6_M0_VI_BT1120_D14_UART5_CTS_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), U5.14
/MIPI_I2C_SCL: U1.5 (VI_BT656_D3_M0_VI_BT1120_D11_UART5_TX_M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), U5.16
/MIPI_I2C_SDA: U1.7 (VI_BT656_D4_M0_VI_BT1120_D12_UART5_RX_M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), U5.17
/MIPI/LVDS_CLK1_N: U1.119 (VI_BT1120_D2_LVDS_RX_CLK1N_MIPI_CSI_RX_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), U5.1
/MIPI/LVDS_CLK1_P: U1.120 (VI_BT1120_D3_LVDS_RX_CLK1P_MIPI_CSI_RX_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), U5.2
/MIPI/LVDS_CLK_N: U1.125 (VI_BT656_D0_M0_VI_BT1120_D8_LVDS_RX_CLK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), U5.9
/MIPI/LVDS_CLK_P: U1.126 (VI_BT656_D1_M0_VI_BT1120_D9_LVDS_RX_CLK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), U5.10
/MIPI/LVDS_D0_N: U1.127 (VI_BT656_CLK_M0_VI_BT1120_CLK_LVDS_RX_D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), U5.11
/MIPI/LVDS_D0_P: U1.128 (LVDS_RX_D0P_MIPI_CSI_RX_D0P_VI_CIF_HREF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), U5.12
/MIPI/LVDS_D1_N: U1.123 (VI_BT1120_D6_LVDS_RX_D1N_MIPI_CSI_RX_D1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), U5.7
/MIPI/LVDS_D1_P: U1.124 (VI_BT1120_D7_LVDS_RX_D1P_MIPI_CSI_RX_D1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), U5.8
/MIPI/LVDS_D2_N: U1.121 (VI_BT1120_D4_LVDS_RX_D2N_MIPI_CSI_RX_D2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), U5.5
/MIPI/LVDS_D2_P: U1.122 (VI_BT1120_D5_LVDS_RX_D2P_MIPI_CSI_RX_D2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), U5.6
/MIPI/LVDS_D3_N: U1.117 (VI_BT1120_D0_LVDS_RX_D3N_MIPI_CSI_RX_D3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), U5.3
/MIPI/LVDS_D3_P: U1.118 (VI_BT1120_D1_LVDS_RX_D3P_MIPI_CSI_RX_D3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), U5.4
/MIPI/LVDS_MCLK0: R6.1, U5.19
/MIPI/LVDS_MCLK1: R7.1, U5.20
/MIPI/LVDS_RST1: U1.9 (VI_BT656_D7_M0_VI_BT1120_D15_PWM1_M2_VI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), U5.13
/NPOR: U1.66 (nPOR), U5.74
/SDMMC_CLK: R22.1, R50.2
/SDMMC_CMD: R49.2, U1.16 (JTAG_LPMCU_TMS_M1_I2C0_SDA_M2_PWM11_IR_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)
/SDMMC_D0: R45.2, U1.14 (PWM8_M0_UART2_RX_M0_SDMMC_D0_GPIO3_A3_u)
/SDMMC_D1: R46.2, U1.12 (PWM9_M0_UART2_TX_M0_SDMMC_D1_GPIO3_A2_u)
/SDMMC_D2: R47.2, U1.18 (JTAG_HPMCU_TCK_M1_JTAG_CPU_TCK_M0_UART5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)
/SDMMC_D3: R48.2, U1.17 (JTAG_HPMCU_TMS_M1_JTAG_CPU_TMS_M0_UART5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)
/SDMMC_DET: R29.1, R44.2, U1.11 (SDMMC_DET_GPIO3_A1_u)
/USB_DET_IN: U1.25 (USB_VBUSDET), U5.24
/USB_N: U1.26 (USB_DM), U5.22
/USB_P: U1.27 (USB_DP), U5.23
/VDDi: C62.1, U9.C2 (VDDi)
GND: C1.2, C2.1, C3.2, C4.2, C5.2, C6.2, C7.2, C8.2, C9.2, C10.2, C11.2, C12.2, C13.2, C14.2, C15.2, C16.2, C17.2, C18.2, C19.2, C20.2, C21.2, C22.2, C23.2, C24.2, C25.2, C26.2, C27.2, C28.2, C29.2, C30.2, C31.2, C32.2, C33.2, C34.2, C35.2, C36.2, C38.1, C39.1, C40.1, C41.1, C43.1, C44.1, C46.2, C47.2, C48.2, C49.2, C50.2, C51.2, C52.2, C53.2, C54.2, C55.2, C56.2, C58.2, C59.2, C60.2, C61.2, C62.2, C63.2, C64.2, C65.2, C66.2, C67.2, C68.2, C69.2, C70.2, J1.1, J1.3, R9.1, R15.2, R17.2, R20.2, R23.2, R24.2, R25.1, R29.2, U1.57 (TVSS), U1.129 (ePAD), U2.2 (GND), U3.1 (GND3), U3.4 (GND2), U3.5 (GND2), U3.12 (GND1), U3.13 (GND1), U3.15 (AGND), U3.17 (AGND), U3.21 (AGND), U5.21, U5.25, U5.28, U5.29, U5.36, U5.55, U5.56, U5.57, U5.75, U5.82, U5.83, U5.84, U5.89, U5.112, U7.2 (GND), U7.4 (GND), U8.2 (GND), U9.A6 (VSS2), U9.C4 (VSS3), U9.E7 (VSS4), U9.G5 (VSS5), U9.H10 (VSS6), U9.J5 (VSS1), U9.K8 (VSSQ1), U9.N2 (VSSQ2), U9.N5 (VSSQ3), U9.P4 (VSSQ4), U9.P6 (VSSQ5)
unnamed: C28.1, C29.1, L2.2
unnamed: C57.1, C58.1, J1.2
unnamed: R34.1, U5.37
unnamed: R35.1, U5.38
unnamed: R36.1, U5.39
unnamed: R37.1, U5.40
unnamed: R38.1, U5.41
unnamed: R39.1, U5.42
unnamed: R40.1, U5.43
unnamed: R41.1, U5.44
unnamed: R42.1, U5.45
unnamed: R43.1, U5.46
unnamed: R44.1, U5.48
unnamed: R45.1, U5.49
unnamed: R46.1, U5.50
unnamed: R47.1, U5.51
unnamed: R48.1, U5.52
unnamed: R49.1, U5.53
unnamed: R50.1, U5.54
unnamed: R51.1, U5.63
unnamed: R52.1, U5.64
unnamed: R53.1, U5.69
unnamed: R54.1, U5.68
unnamed: C6.1, U1.21 (OSC_RTC_XIN), Y1.1
unnamed: C7.1, U1.20 (OSC_RTC_XOUT), Y1.2
unnamed: C2.2, R1.1, U1.68 (OSC_SOC_XIN), U7.1 (X1)
unnamed: R1.2, R2.2, U1.69 (OSC_SOC_XOUT)
unnamed: L1.1, U1.96 (OTP_AVDD1V8_ETH_AVDD1V8_TSADC_AVDD1V8)
unnamed: C8.1, R3.2, U1.19 (RTC_AVDD3V3)
unnamed: R21.2, U1.48 (FSPI_CLK_EMMC_CLK_GPIO4_B1_d)
unnamed: R22.2, U1.15 (JTAG_LPMCU_TCK_M1_I2C0_SCL_M2_PWM10_M0_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)
unnamed: R4.2, U1.85 (I2C3_SCL_M1_AUD_DSM_N_UART5_TX_M1_PWM11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)
unnamed: R6.2, U1.2 (MIPI_CLK0_OUT_VI_CIF_CLKO_M0_GPIO3_C4_d)
unnamed: R7.2, U1.4 (VI_BT656_D2_M0_VI_BT1120_D10_PWM7_IR_M2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)
unnamed: R25.2, U1.37 (CODEC_AVSS)
unnamed: C53.1, U1.30 (CODEC_VCM)
unnamed: R23.1, U1.52 (DRAM_ZQ)
unnamed: L7.2, U1.101 (FEPHY_AVDD3V3)
unnamed: R24.1, U1.102 (FEPHY_REXT)
unnamed: C54.1, R26.2, U1.24 (SARADC_USB_AVDD1V8)
unnamed: R8.1, U2.5 (EN)
unnamed: R9.2, R10.2, U2.1 (FB)
unnamed: L3.1, U2.4 (SW)
unnamed: C37.2, R14.1, R15.1, U3.14 (FB1)
unnamed: C42.2, R16.1, R17.1, U3.3 (FB2)
unnamed: C45.2, R19.1, R20.1, U3.2 (FB3)
unnamed: L5.2, U3.6 (LX2)
unnamed: L6.2, U3.20 (LX3)
unnamed: L4.2, U3.11 (LX)
unnamed: C46.1, U3.16 (VCC)
unnamed: C49.1, U3.10 (VIN1)
unnamed: C48.1, U3.7 (VIN2)
unnamed: C47.1, U3.19 (VIN3)
unnamed: C1.1, R2.1, U7.3 (X2)
unnamed: C68.1, C69.1, C70.1, U9.E6 (VCC1), U9.F5 (VCC2), U9.J10 (VCC3), U9.K9 (VCC4)
unnamed: C63.1, C64.1, C65.1, C66.1, C67.1, U9.C6 (VCCQ1), U9.M4 (VCCQ2), U9.N4 (VCCQ3), U9.P3 (VCCQ4), U9.P5 (VCCQ5)
VCC1V8_MICBIAS: U1.32 (CODEC_MICBIAS), U5.31
VCC3V3_RTC: D1.1 (K), R3.1, U5.76
VCC5V0_SYS: C30.1, C31.1, C60.1, R8.2, R11.1, R12.1, R13.1, U2.3 (VIN), U5.79, U5.80, U5.81, U8.1 (IN), U8.3 (CE)
VCCIO_FLASH: C50.1, R55.2, R56.2, R57.2, U1.43 (VCCIO3_VCC)
VCC_1V8: C3.1, C4.1, C26.1, C27.1, C43.2, C44.2, C45.1, L1.2, L2.1, L6.1, R5.1, R19.2, R26.1, U1.53 (DDR_PLL_AVDD1V8), U1.70 (OSC_AVDD1V8_PLL_AVDD1V8), U5.77
VCC_3V3: C9.1, C10.1, C37.1, C38.2, C39.2, C51.1, C52.1, C55.1, D1.2 (A), L4.1, L7.1, R14.2, U1.13 (VCCIO4_VCC), U1.28 (USB_AVDD3V3), U1.61 (PMU_VCC3V3), U1.81 (VCCIO1_VCC3V3), U1.88 (VCCIO6_VCC), U1.108 (VCCIO5_VCC), U5.78
VCC_DDR: C22.1, C23.1, C24.1, C25.1, C32.1, C33.1, L3.2, R10.1, U1.49 (DDR_VDDQ_1), U1.50 (DDR_VDDQ_2), U1.56 (DDR_VDDQ_3), U2.6 (OUT)
VDD_0V9: C5.1, C12.1, C13.1, C14.1, C15.1, C16.1, C17.1, C18.1, C40.2, C41.2, C42.1, L5.1, R16.2, R18.1, U1.10 (DVDD_1), U1.51 (DVDD_2), U1.54 (DVDD_3), U1.55 (DVDD_4), U1.67 (OSC_DVDD0V9_PMU_DVDD0V9), U1.71 (PLL_DVDD0V9), U1.82 (DVDD_5), U1.103 (DVDD_6), U1.116 (DVDD_7)
VDD_ARM: C19.1, C20.1, C21.1, R18.2, U1.115 (CPU_DVDD)
